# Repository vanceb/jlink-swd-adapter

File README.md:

# jlink-swd-adapter
An Adapter from 20 pin JLink IDC to 6 pin IDC for SWD

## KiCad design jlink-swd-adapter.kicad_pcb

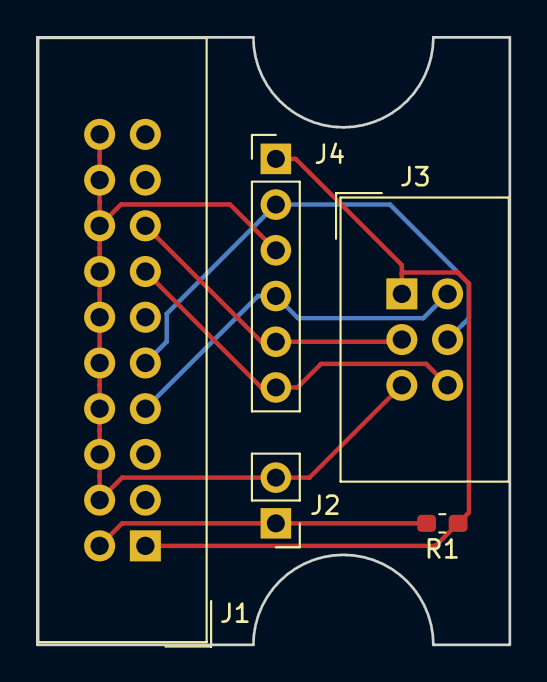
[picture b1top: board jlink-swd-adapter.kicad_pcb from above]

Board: 2 copper layers, 26.2 x 33.8 mm, 5 parts (0 on the bottom side), 7 nets.

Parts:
J1: 20-WAY JLINK IDC; IDC-Header_2x10_P2.54mm_Vertical
J2: POWER; PinHeader_1x02_P2.54mm_Vertical
J3: 6-WAY SWD IDC; IDC-Header_2x03_P2.54mm_Vertical
J4: ST NUCLEO DEBUG; PinHeader_1x06_P2.54mm_Vertical
R1: 0R Link; R_0603_1608Metric_Pad1.05x0.95mm_HandSolder

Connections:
GND: J1.4, J1.6, J1.8, J1.10, J1.12, J1.14, J1.16, J1.18, J1.20, J2.2, J3.5, J4.3
SWCLK: J1.9, J3.4, J4.2
SWDIO: J1.7, J3.2, J4.4
SWO: J1.13, J3.6, J4.6
VCC: J1.2, J2.1, R1.2
VTREF: J1.1, J3.1, J4.1, R1.1
~RESET: J1.15, J3.3, J4.5

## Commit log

2019-04-30 PCB Gerbers
